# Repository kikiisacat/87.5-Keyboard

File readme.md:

# 87.5% Keyboard

I made a custom RP-Pico keyboard with the arrow keys integrated in the number pad and main keyboard to save space and look nice. Additionally, the FN keys are remapped and can be triggered from holding down the FN/FN lock key and using 1,2,3,4,5,6,7,8,9,0,-,= keys for F1-F12 to save more space.

# Features
77 switches + a rotary encoder push button \
Hold FN and press 1-0, -, = for F1-F12 \
New FN lock and Macro lock keys for ease of use \
24 macro slots in firmware \
LED indicators for FN lock, Caps lock, and Macro lock. \
QMK firmware \
RP Pico mounted on headers to save space

# Schematic wiring & PCB

# Final Assembly

Most of the keycaps' STEP files were from this repo: \
https://github.com/anhthang/dsa-keycap \
For the custom length keycaps like enter, I would split a 1x1 keycap in half and extrude the ends together to meet the new length. \
I decided to make the spacebar myself because the custom length keycaps looked worse as they got longer. I didn't realize the repo had a spacebar until after I was done.

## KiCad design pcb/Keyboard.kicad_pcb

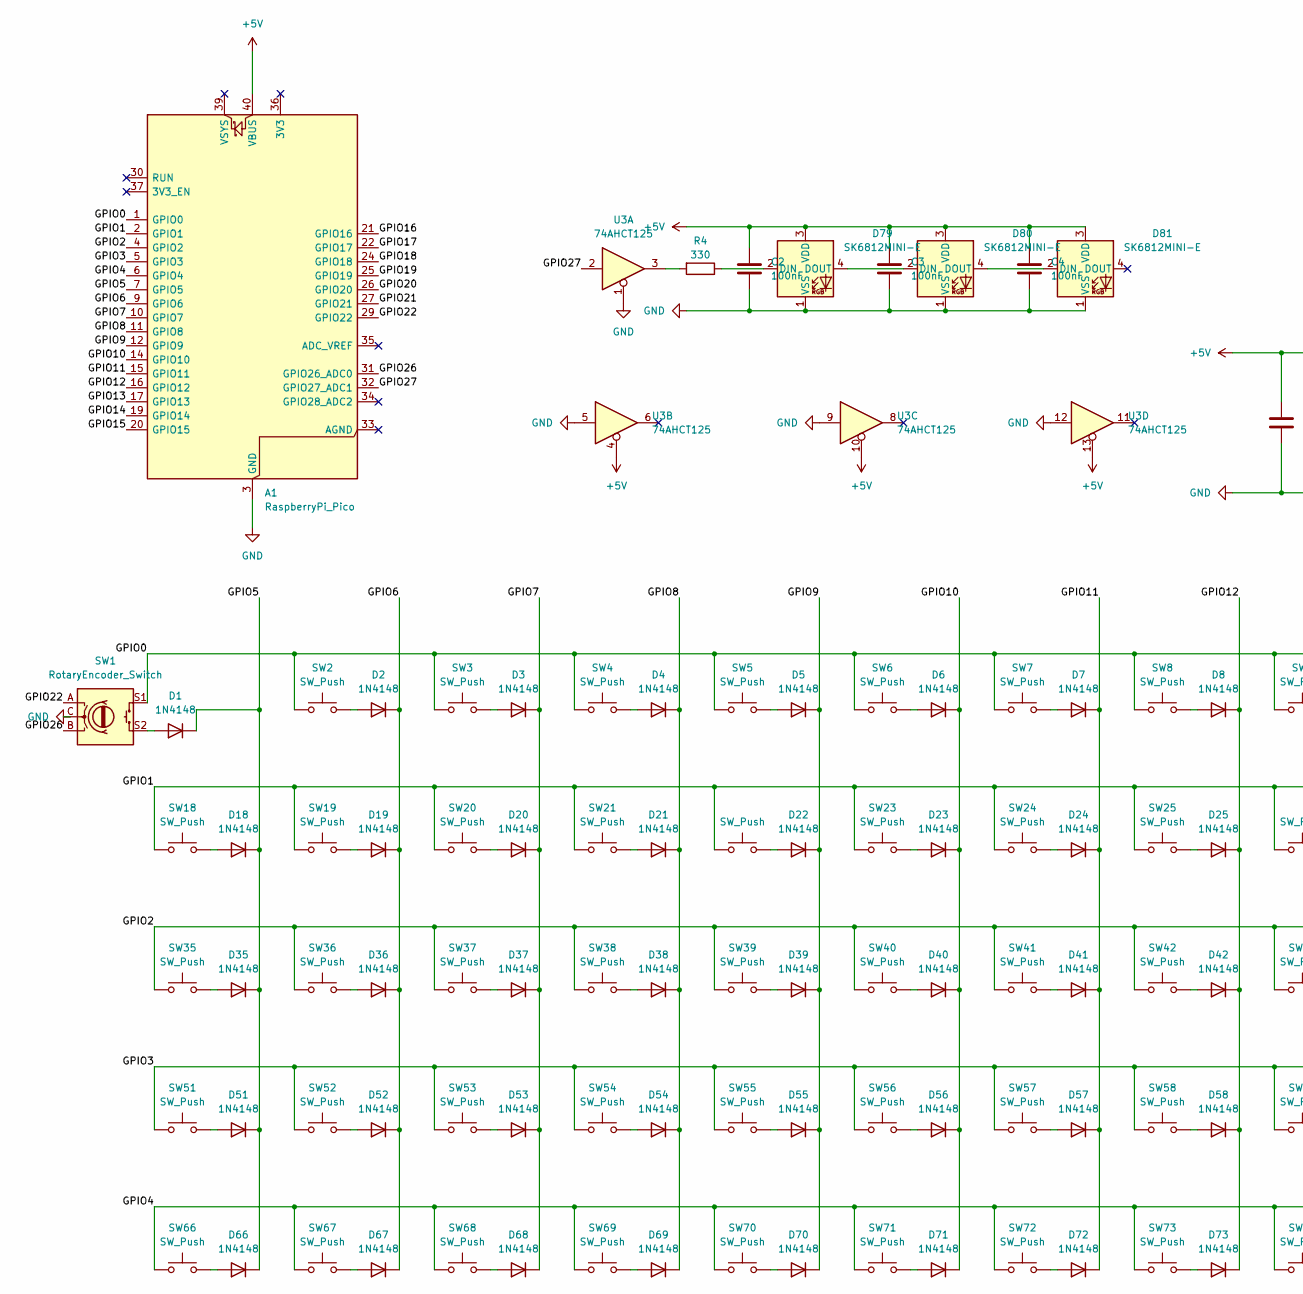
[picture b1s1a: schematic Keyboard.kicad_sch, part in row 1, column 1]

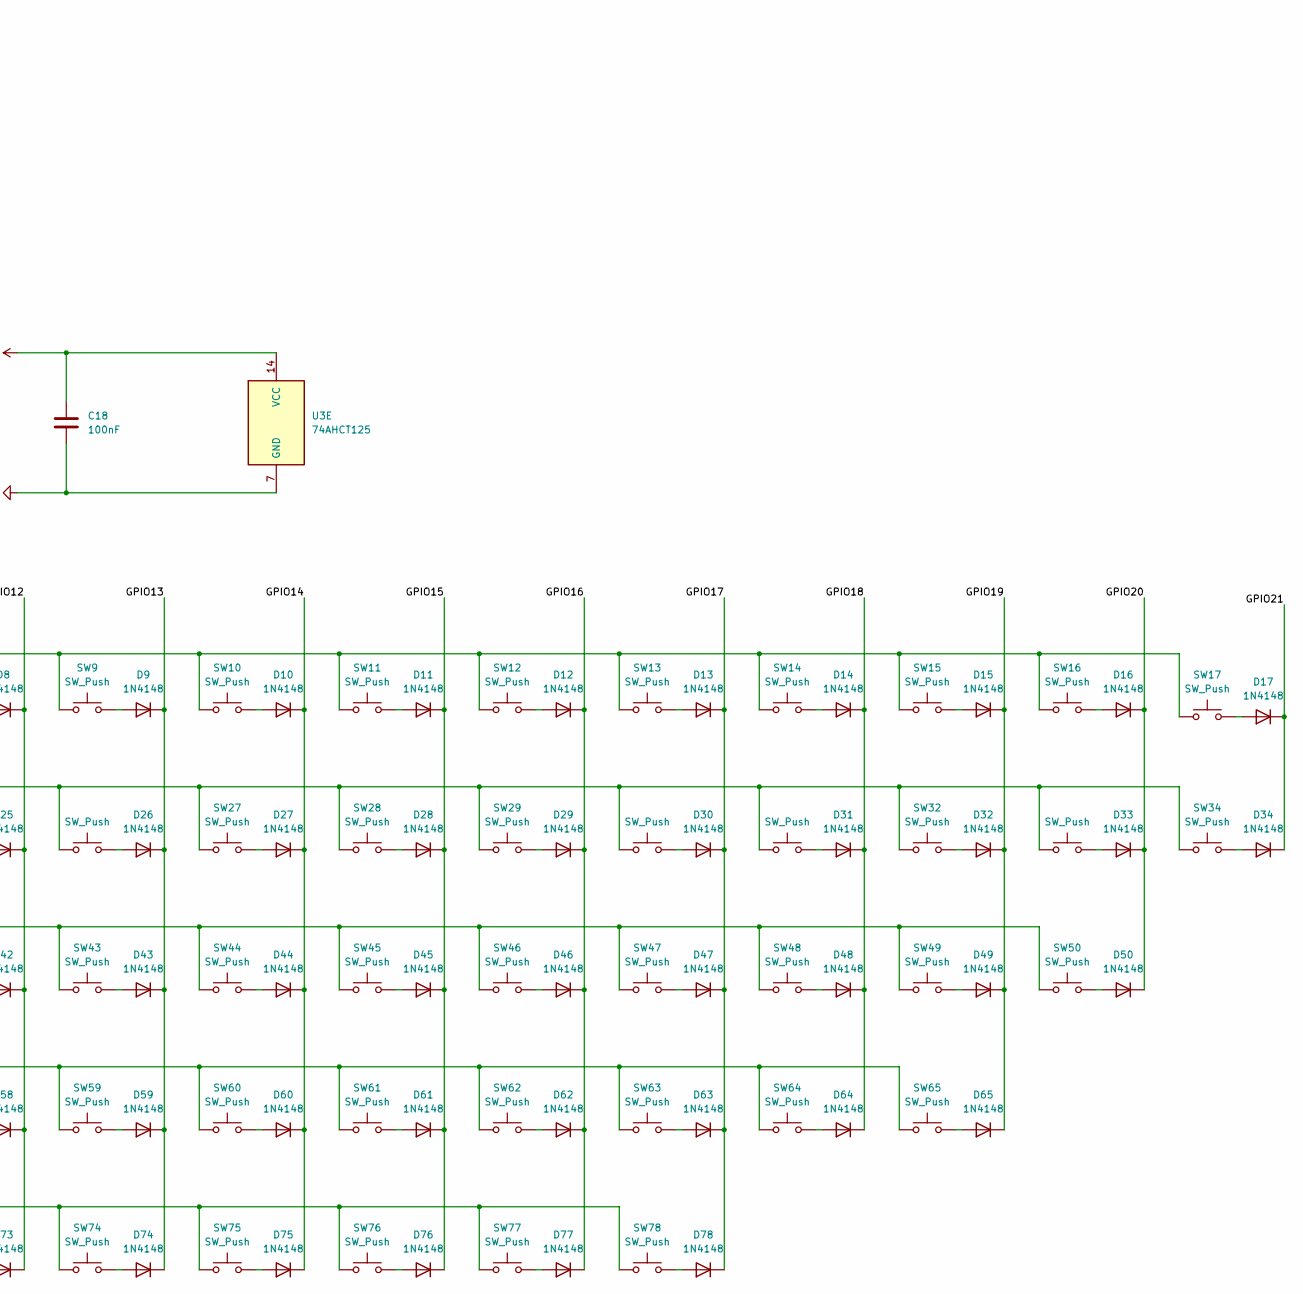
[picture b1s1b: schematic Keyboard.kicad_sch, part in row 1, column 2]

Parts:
A1: RaspberryPi_Pico; RaspberryPi_Pico_PinHeaders
C2, C3, C4, C18: 100nF; C_0805_2012Metric
D1, D2, D3, D4, D5, D6, D7, D8, D9, D10, D11, D12, D13, D14, D15, D16, D17, D18, D19, D20, D21, D22, D23, D24, D25, D26, D27, D28, D29, D30, D31, D32, D33, D34, D35, D36, D37, D38, D39, D40, D41, D42, D43, D44, D45, D46, D47, D48, D49, D50, D51, D52, D53, D54, D55, D56, D57, D58, D59, D60, D61, D62, D63, D64, D65, D66, D67, D68, D69, D70, D71, D72, D73, D74, D75, D76, D77, D78: 1N4148; D_DO-35_SOD27_P7.62mm_Horizontal
D79, D80, D81: SK6812MINI-E; LED_SK6812MINI-E_3.2x2.8mm_P1.5mm_ReverseMount
R4: 330; R_0805_2012Metric
SW1: RotaryEncoder_Switch; RotaryEncoder_Alps_EC11E-Switch_Vertical_H20mm
SW2, SW3, SW4, SW5, SW6, SW7, SW8, SW9, SW10, SW11, SW12, SW13, SW14, SW15, SW16, SW17, SW18, SW19, SW20, SW21, SW22, SW23, SW24, SW25, SW26, SW27, SW28, SW29, SW30, SW31, SW32, SW33, SW34, SW35, SW36, SW37, SW38, SW39, SW40, SW41, SW42, SW43, SW44, SW45, SW46, SW47, SW48, SW49, SW50, SW51, SW52, SW53, SW54, SW55, SW56, SW57, SW58, SW59, SW60, SW61, SW62, SW63, SW64, SW65, SW66, SW67, SW68, SW69, SW70, SW71, SW72, SW73, SW74, SW75, SW76, SW77, SW78: SW_Push; SW_Cherry_MX_1.00u_PCB
U3: 74AHCT125; DIP-14_W7.62mm

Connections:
+5V: A1.40 (VBUS), C2.1, C3.1, C4.1, C18.1, D79.3 (VDD), D80.3 (VDD), D81.3 (VDD), U3.4, U3.10, U3.13, U3.14 (VCC)
/GPIO0: A1.1 (GPIO0), SW1.S1, SW2.1, SW3.1, SW4.1, SW5.1, SW6.1, SW7.1, SW8.1, SW9.1, SW10.1, SW11.1, SW12.1, SW13.1, SW14.1, SW15.1, SW16.1, SW17.1
/GPIO1: A1.2 (GPIO1), SW18.1, SW19.1, SW20.1, SW21.1, SW22.1, SW23.1, SW24.1, SW25.1, SW26.1, SW27.1, SW28.1, SW29.1, SW30.1, SW31.1, SW32.1, SW33.1, SW34.1
/GPIO2: A1.4 (GPIO2), SW35.1, SW36.1, SW37.1, SW38.1, SW39.1, SW40.1, SW41.1, SW42.1, SW43.1, SW44.1, SW45.1, SW46.1, SW47.1, SW48.1, SW49.1, SW50.1
/GPIO3: A1.5 (GPIO3), SW51.1, SW52.1, SW53.1, SW54.1, SW55.1, SW56.1, SW57.1, SW58.1, SW59.1, SW60.1, SW61.1, SW62.1, SW63.1, SW64.1, SW65.1
/GPIO4: A1.6 (GPIO4), SW66.1, SW67.1, SW68.1, SW69.1, SW70.1, SW71.1, SW72.1, SW73.1, SW74.1, SW75.1, SW76.1, SW77.1, SW78.1
/GPIO5: A1.7 (GPIO5), D1.1 (K), D18.1 (K), D35.1 (K), D51.1 (K), D66.1 (K)
/GPIO6: A1.9 (GPIO6), D2.1 (K), D19.1 (K), D36.1 (K), D52.1 (K), D67.1 (K)
/GPIO7: A1.10 (GPIO7), D3.1 (K), D20.1 (K), D37.1 (K), D53.1 (K), D68.1 (K)
/GPIO8: A1.11 (GPIO8), D4.1 (K), D21.1 (K), D38.1 (K), D54.1 (K), D69.1 (K)
/GPIO9: A1.12 (GPIO9), D5.1 (K), D22.1 (K), D39.1 (K), D55.1 (K), D70.1 (K)
/GPIO10: A1.14 (GPIO10), D6.1 (K), D23.1 (K), D40.1 (K), D56.1 (K), D71.1 (K)
/GPIO11: A1.15 (GPIO11), D7.1 (K), D24.1 (K), D41.1 (K), D57.1 (K), D72.1 (K)
/GPIO12: A1.16 (GPIO12), D8.1 (K), D25.1 (K), D42.1 (K), D58.1 (K), D73.1 (K)
/GPIO13: A1.17 (GPIO13), D9.1 (K), D26.1 (K), D43.1 (K), D59.1 (K), D74.1 (K)
/GPIO14: A1.19 (GPIO14), D10.1 (K), D27.1 (K), D44.1 (K), D60.1 (K), D75.1 (K)
/GPIO15: A1.20 (GPIO15), D11.1 (K), D28.1 (K), D45.1 (K), D61.1 (K), D76.1 (K)
/GPIO16: A1.21 (GPIO16), D12.1 (K), D29.1 (K), D46.1 (K), D62.1 (K), D77.1 (K)
/GPIO17: A1.22 (GPIO17), D13.1 (K), D30.1 (K), D47.1 (K), D63.1 (K), D78.1 (K)
/GPIO18: A1.24 (GPIO18), D14.1 (K), D31.1 (K), D48.1 (K), D64.1 (K)
/GPIO19: A1.25 (GPIO19), D15.1 (K), D32.1 (K), D49.1 (K), D65.1 (K)
/GPIO20: A1.26 (GPIO20), D16.1 (K), D33.1 (K), D50.1 (K)
/GPIO21: A1.27 (GPIO21), D17.1 (K), D34.1 (K)
/GPIO22: A1.29 (GPIO22), SW1.A
/GPIO26: A1.31 (GPIO26_ADC0), SW1.B
/GPIO27: A1.32 (GPIO27_ADC1), U3.2
GND: A1.3 (GND), A1.8 (GND), A1.13 (GND), A1.18 (GND), A1.23 (GND), A1.28 (GND), A1.38 (GND), C2.2, C3.2, C4.2, C18.2, D79.1 (VSS), D80.1 (VSS), D81.1 (VSS), SW1.C, U3.1, U3.5, U3.7 (GND), U3.9, U3.12
unnamed: D1.2 (A), SW1.S2
unnamed: D2.2 (A), SW2.2
unnamed: D3.2 (A), SW3.2
unnamed: D4.2 (A), SW4.2
unnamed: D5.2 (A), SW5.2
unnamed: D6.2 (A), SW6.2
unnamed: D7.2 (A), SW7.2
unnamed: D8.2 (A), SW8.2
unnamed: D9.2 (A), SW9.2
unnamed: D10.2 (A), SW10.2
unnamed: D11.2 (A), SW11.2
unnamed: D12.2 (A), SW12.2
unnamed: D13.2 (A), SW13.2
unnamed: D14.2 (A), SW14.2
unnamed: D15.2 (A), SW15.2
unnamed: D16.2 (A), SW16.2
unnamed: D17.2 (A), SW17.2
unnamed: D18.2 (A), SW18.2
unnamed: D19.2 (A), SW19.2
unnamed: D20.2 (A), SW20.2
unnamed: D21.2 (A), SW21.2
unnamed: D22.2 (A), SW22.2
unnamed: D23.2 (A), SW23.2
unnamed: D24.2 (A), SW24.2
unnamed: D25.2 (A), SW25.2
unnamed: D26.2 (A), SW26.2
unnamed: D27.2 (A), SW27.2
unnamed: D28.2 (A), SW28.2
unnamed: D29.2 (A), SW29.2
unnamed: D30.2 (A), SW30.2
unnamed: D31.2 (A), SW31.2
unnamed: D32.2 (A), SW32.2
unnamed: D33.2 (A), SW33.2
unnamed: D34.2 (A), SW34.2
unnamed: D35.2 (A), SW35.2
unnamed: D36.2 (A), SW36.2
unnamed: D37.2 (A), SW37.2
unnamed: D38.2 (A), SW38.2
unnamed: D39.2 (A), SW39.2
unnamed: D40.2 (A), SW40.2
unnamed: D41.2 (A), SW41.2
unnamed: D42.2 (A), SW42.2
unnamed: D43.2 (A), SW43.2
unnamed: D44.2 (A), SW44.2
unnamed: D45.2 (A), SW45.2
unnamed: D46.2 (A), SW46.2
unnamed: D47.2 (A), SW47.2
unnamed: D48.2 (A), SW48.2
unnamed: D49.2 (A), SW49.2
unnamed: D50.2 (A), SW50.2
unnamed: D51.2 (A), SW51.2
unnamed: D52.2 (A), SW52.2
unnamed: D53.2 (A), SW53.2
unnamed: D54.2 (A), SW54.2
unnamed: D55.2 (A), SW55.2
unnamed: D56.2 (A), SW56.2
unnamed: D57.2 (A), SW57.2
unnamed: D58.2 (A), SW58.2
unnamed: D59.2 (A), SW59.2
unnamed: D60.2 (A), SW60.2
unnamed: D61.2 (A), SW61.2
unnamed: D62.2 (A), SW62.2
unnamed: D63.2 (A), SW63.2
unnamed: D64.2 (A), SW64.2
unnamed: D65.2 (A), SW65.2
unnamed: D66.2 (A), SW66.2
unnamed: D67.2 (A), SW67.2
unnamed: D68.2 (A), SW68.2
unnamed: D69.2 (A), SW69.2
unnamed: D70.2 (A), SW70.2
unnamed: D71.2 (A), SW71.2
unnamed: D72.2 (A), SW72.2
unnamed: D73.2 (A), SW73.2
unnamed: D74.2 (A), SW74.2
unnamed: D75.2 (A), SW75.2
unnamed: D76.2 (A), SW76.2
unnamed: D77.2 (A), SW77.2
unnamed: D78.2 (A), SW78.2
unnamed: D79.2 (DIN), R4.1
unnamed: D79.4 (DOUT), D80.2 (DIN)
unnamed: D80.4 (DOUT), D81.2 (DIN)
unnamed: R4.2, U3.3

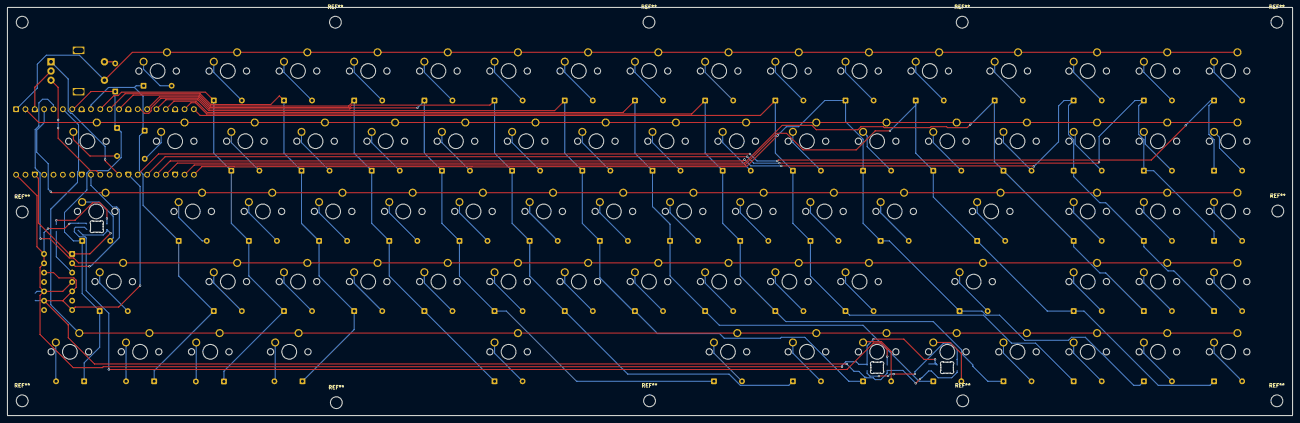
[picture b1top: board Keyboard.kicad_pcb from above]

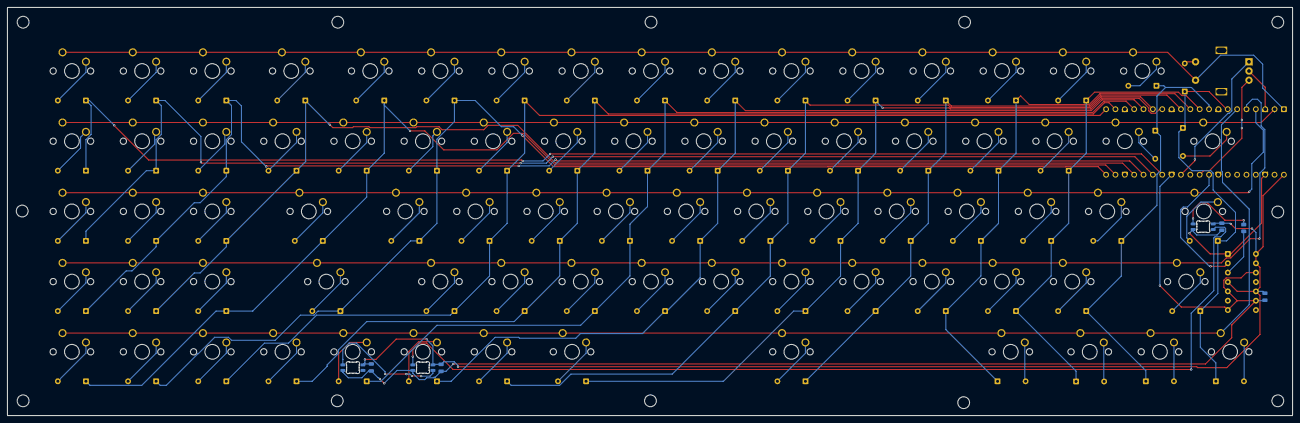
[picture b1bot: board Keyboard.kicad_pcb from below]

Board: 2 copper layers, 348.8 x 110.8 mm, 166 parts (88 on the bottom side), 109 nets.
